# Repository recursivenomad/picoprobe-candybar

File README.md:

🍫 **A charming debug probe using the Raspberry Pi Pico**
=========================================================

### With a custom breakout, interface, and enclosure for Raspberry Pi's [Debug Probe][URL-Debug-Probe] firmware

[][URL-Repository]

***Features***
==============

Quick in-progress list:
- Logic level-shifting for interfacing with 5V/2.5V/1.8V boards (left switch)
- Power output selection (5V/none/3.3V) (right switch)
- 2 hardware interrupt breakpoints (rising & falling edge; left side pins)
- 9 pins wired for future implementation of a logic analyzer (3 analog, 3 logic level-shifted digital, 3 raw digital)
- Status LEDs (UART RX/TX, debug CONNECTED/RUNNING)
- Power rocker switch
- Debug access port for debugging with a second Picoprobe Candybar

***Cloning***
=============

```bash
git clone https://gitlab.com/recursivenomad/picoprobe-candybar.git
cd picoprobe-candybar/
git submodule update --init --single-branch
cd firmware/lib/debugprobe/
git config --local submodule.CMSIS_5.branch master
GIT_LFS_SKIP_SMUDGE=1 git submodule update --init --depth 1
git submodule foreach 'git fetch --depth 1'   # redundant, but gets the checked-out tag
cd ../../..
```

&nbsp;

***License / Access***
======================

This original work is freely available under your choice of the [*MIT-0*](./LICENSE.txt) license or [*CC0-1.0*][URL-CC0] public domain dedication.  
Although attribution is not required, sharing when you've made something with my work is really cool 💖

<details> <summary> <b><i>This work as a whole contains greater source code restrictions, fully listed here:</i></b> </summary>

  > Importing the [Debug Probe](https://github.com/raspberrypi/debugprobe/tree/debugprobe-v2.0.1/) submodule from Raspberry Pi introduces the following restrictions:  
  > *Linked to in [`./firmware/lib/`](./firmware/lib/)*
  >   - [*MIT License*][URL-MIT]
  >   - [*3-Clause BSD License*][URL-BSD-3-Clause]
  >   - [*Apache License, Version 2.0*][URL-Apache-2.0]
  >
  > Binaries are built using the [Pico SDK][URL-Pico-SDK] and [Arm GNU Toolchain][URL-ARM-Toolchain], and will add the following notices for distribution:
  >   - [*GCC Runtime Library Exception*][URL-GCC-Exception]
  >   - [*SunPro License*][URL-SunPro]
  >   - [*OAR License*][URL-OAR]
  >   - [*BSD 4.3 TAHOE License*][URL-BSD-4.3TAHOE]
  >   - [*Martin Birgmeier License*][URL-Martin-Birgmeier]

</details>

----------------------

*Repository: <https://gitlab.com/recursivenomad/picoprobe-candybar/>*  
*Contact: <recursivenomad@protonmail.com>*

----------------------

[URL-MIT-0]: <https://opensource.org/license/mit-0/>
[URL-CC0]: <https://creativecommons.org/publicdomain/zero/1.0/>

[URL-MIT]: <https://opensource.org/license/mit>
[URL-BSD-3-Clause]: <https://opensource.org/license/bsd-3-clause>
[URL-Apache-2.0]: <https://opensource.org/license/apache-2-0>

[URL-GCC-Exception]: <https://www.gnu.org/licenses/gcc-exception-3.0.en.html>
[URL-SunPro]: <https://spdx.org/licenses/SunPro.html>
[URL-OAR]: <https://spdx.org/licenses/OAR.html>
[URL-BSD-4.3TAHOE]: <https://spdx.org/licenses/BSD-4.3TAHOE.html>
[URL-Martin-Birgmeier]: <https://spdx.org/licenses/Martin-Birgmeier.html>

[URL-Repository]: <https://gitlab.com/recursivenomad/picoprobe-candybar/>

[URL-ARM-Toolchain]: <https://developer.arm.com/Tools%20and%20Software/GNU%20Toolchain>
[URL-Debug-Probe]: <https://github.com/raspberrypi/debugprobe/>
[URL-Pico-SDK]: <https://github.com/raspberrypi/pico-sdk>

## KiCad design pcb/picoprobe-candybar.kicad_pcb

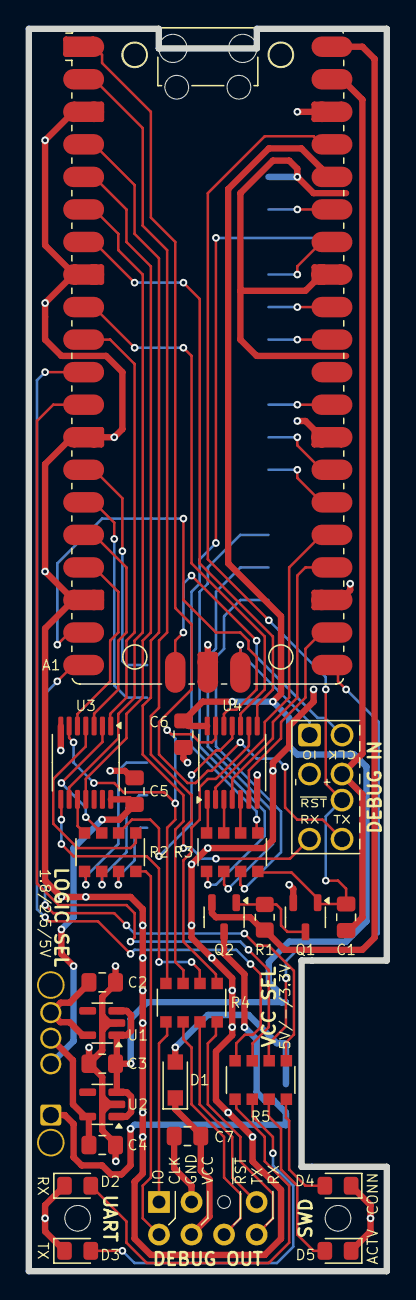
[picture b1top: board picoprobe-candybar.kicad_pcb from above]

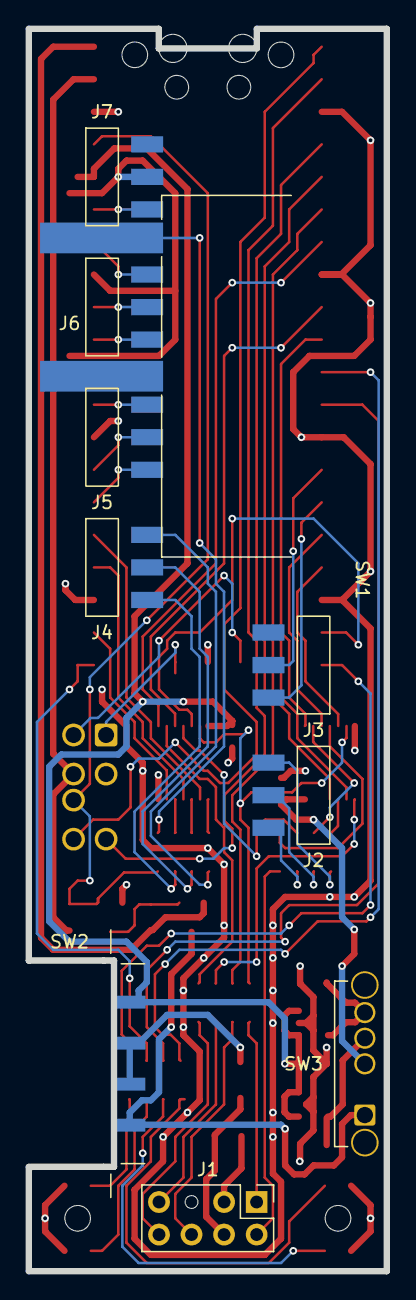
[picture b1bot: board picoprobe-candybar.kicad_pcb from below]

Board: 2 copper layers, 27.9 x 97.0 mm, 35 parts (10 on the bottom side), 68 nets.

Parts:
A1: RaspberryPi_Pico; RaspberryPi_Pico_Original_SMD_HandSolder
C1, C2, C3, C4, C5, C6, C7: 1u; C_0805_2012Metric_Pad1.18x1.45mm_HandSolder
D1: PMEG2010ER; Nexperia_CFP3_SOD-123W
D2: Orange; LED_0805_2012Metric_Pad1.15x1.40mm_HandSolder
D3: Yellow; LED_0805_2012Metric_Pad1.15x1.40mm_HandSolder
D4: Green; LED_0805_2012Metric_Pad1.15x1.40mm_HandSolder
D5: Red; LED_0805_2012Metric_Pad1.15x1.40mm_HandSolder
J0: SWD-UART_PicoprobeCandybar; SWD-UART_PicoprobeCandybar_PressFit_Compact
J1: PinHeader_2x04; PinHeader_2x04_P2.54mm_Vertical
J2, J3, J4, J5, J6, J7: PinHeader_1x03; PinHeader_1x03_P2.54mm_Horizontal_SMD
Q1: SSF2320Y; SOT-23-3
Q2: GSFC02501; SOT-23-3
R1: 100k; R_0805_2012Metric_Pad1.20x1.40mm_HandSolder
R2, R3, R4: 100R; R_Array_Convex_4x1206
R5: 470R; R_Array_Convex_4x1206
SW1: SW-R1-1A-E-1-0; SW_Rocker_SPST_QuickConnect_P10.8mm_SW-R1-1X-E-XX-0_Retrofi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
SW2: SLW-156646-5A-N-D; SW_Slide_SP3T_P3.2mm_CUI_SLW-156646-5A-N-D_Retrofit-SMD-Hor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
SW3: SLW-1277545-2A-RA-S-D; SW_Slide_SP3T_Common_Horizontal_P2mm_CUI_SLW-1277545-2A-RA-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
U1: TLV77318PDBVR; SOT-23-5
U2: TLV77325PDBVR; SOT-23-5
U3, U4: SN74LV6T17PWR; TSSOP-14_4.4x5mm_P0.65mm

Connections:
1V8: C2.1, SW3.4, U1.5 (OUT)
2V5: C4.1, SW3.3, U2.5 (OUT)
3V3: A1.36 (3V3), C3.1, C6.1, SW2.1, U1.1 (IN), U1.3 (EN), U2.1 (IN), U2.3 (EN), U4.14 (VCC)
5V: Q2.3 (D), SW2.4, SW3.1
/3V3_EN: A1.37 (3V3_EN), C1.2, J0.6 (~RESET), Q1.1 (G), R3.4 (R4.1)
/ADC0: A1.31 (GPIO26_ADC0), J6.1
/ADC1: A1.32 (GPIO27_ADC1), J6.2
/ADC2: A1.34 (GPIO28_ADC2), J6.3
/ADC_VREF: A1.35 (ADC_VREF), J7.1
/CB_CLK: J1.2, R2.4 (R4.1)
/CB_CTS: J2.3, R2.3 (R3.1)
/CB_DTR: J2.1, R2.1 (R1.1)
/CB_IO: J1.1, R4.1 (R1.1)
/CB_RS1: J4.1, R3.3 (R3.1)
/CB_RS2: J4.2, R3.2 (R2.1)
/CB_RS3: J4.3, R3.1 (R1.1)
/CB_RS4: A1.26 (GPIO20), J5.1
/CB_RS5: A1.27 (GPIO21), J5.2
/CB_RS6: A1.29 (GPIO22), J5.3
/CB_RTS: J2.2, R2.2 (R2.1)
/CB_RX: J1.8, R4.4 (R4.1)
/CB_TX: J1.7, R4.3 (R3.1)
/CB_~RST: J1.6, R4.2 (R2.1)
/CLK: A1.16 (GPIO12), U3.3 (2A)
/CTS: A1.9 (UART1_CTS), U4.10 (5Y)
/DTR: A1.5 (GPIO3), U3.11 (5A)
/INT_FALL: A1.15 (GPIO11), J3.3
/INT_RISE: A1.14 (GPIO10), J3.2
/IO_IN: A1.19 (GPIO14), U4.12 (6Y)
/IO_OUT: A1.17 (GPIO13), U3.5 (3A)
/IO_SHIFTED: R4.8 (R1.2), U3.6 (3Y), U4.13 (6A)
/LED_CON: A1.20 (GPIO15), R5.5 (R4.2)
/LED_RUN: A1.21 (GPIO16), R5.6 (R3.2)
/LED_RX: A1.12 (GPIO9), R5.7 (R2.2)
/LED_TX: A1.11 (GPIO8), R5.8 (R1.2)
/RS1: A1.22 (GPIO17), U4.6 (3Y)
/RS2: A1.24 (GPIO18), U4.4 (2Y)
/RS3: A1.25 (GPIO19), U4.2 (1Y)
/RTS: A1.10 (UART1_RTS), U3.1 (1A)
/RX: A1.7 (UART1_RX), U4.8 (4Y)
/TX: A1.6 (UART1_TX), U3.9 (4A)
/~RST: A1.4 (GPIO2), R4.7 (R2.2)
AGND: A1.33 (AGND), J7.2
GND: A1.3 (GND), A1.8 (GND), A1.13 (GND), A1.18 (GND), A1.23 (GND), A1.28 (GND), A1.38 (GND), A1.D2 (GND), C2.2, C3.2, C4.2, C5.2, C6.2, C7.2, D2.1 (K), D3.1 (K), D4.1 (K), D5.1 (K), J0.3 (GND), J1.3, J7.3, Q1.2 (S), SW1.1 (A), U1.2 (GND), U2.2 (GND), U3.7 (GND), U4.7 (GND)
unnamed: A1.1 (UART0_TX), J0.8 (UART_RX)
unnamed: A1.2 (UART0_RX), J0.7 (UART_TX)
unnamed: A1.D1 (SWCLK), J0.2 (SWCLK)
unnamed: A1.D3 (SWDIO), J0.1 (SWDIO)
unnamed: D1.2 (A), SW2.2, SW2.3
unnamed: D2.2 (A), R5.1 (R1.1)
unnamed: D3.2 (A), R5.2 (R2.1)
unnamed: D4.2 (A), R5.4 (R4.1)
unnamed: D5.2 (A), R5.3 (R3.1)
unnamed: Q1.3 (D), Q2.1 (G), R1.1
unnamed: R2.8 (R1.2), U3.10 (5Y)
unnamed: R2.7 (R2.2), U3.2 (1Y)
unnamed: R2.6 (R3.2), U4.11 (5A)
unnamed: R2.5 (R4.2), U3.4 (2Y)
unnamed: R3.8 (R1.2), U4.1 (1A)
unnamed: R3.7 (R2.2), U4.3 (2A)
unnamed: R3.6 (R3.2), U4.5 (3A)
unnamed: R3.5 (R4.2), SW1.2 (B)
unnamed: R4.6 (R3.2), U3.8 (4Y)
unnamed: R4.5 (R4.2), U4.9 (4A)
VBUS: A1.40 (VBUS), Q2.2 (S), R1.2
VLOGIC: C5.1, SW3.2, U3.14 (VCC)
VOUT: C7.1, D1.1 (K), J1.4
VSYS: A1.39 (VSYS), C1.1, J0.4 (VCC)

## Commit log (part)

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2024-06-22 Initialize KiCad project
    KiCad 8.0.3
2024-06-23 Add ki-lime-pi-to-go submodule
    Ki-Lime Pi Pico 2.0.0
2024-06-24 Ignore autosaves
2024-06-25 Register compact-title-block
2024-06-30 Add CC0 as elective dual license
2024-06-30 Embrace Ki-Lime Pi Pico library name
2024-06-30 Update kicad-title-block for standardized license
2024-06-30 Remove SPDX text for GitHub's license recognition
2024-06-30 Bump submodules for unified license text
2024-07-03 Add debugprobe submodule
    Debug Probe v2.0.1
2024-07-03 Change PROJECT_NAME
2024-07-03 Override with definitions specific to Candybar
    - Adding target reset support
    - Using the onboard LED for USB indication
    - Applying a custom USB device name
2024-07-03 Remove existing UART feature descriptions
2024-07-03 Create license info binary declaration macros
2024-07-04 Update tools and library path in attributions
2024-07-26 Simplify .gitmodules
2024-07-26 Rename title block directory
2024-07-26 Don't track a specific branch for Ki-Lime Pi Pico
2024-07-26 Add picoprobe-candybar-interface submodule
    Version 0.1.0
2024-07-26 Spacing
2024-07-29 Update picoprobe-candybar-interface submodule
    0.1.1
2024-07-29 Add IDC cable connector
2024-07-29 Ignore .bak files
2024-07-29 Add 74AUP1T17 per Debug Probe schematic
    <https://assets.nexperia.com/documents/data-sheet/74AUP1T17.pdf>
    <https://datasheets.raspberrypi.com/debug/raspberry-pi-debug-probe-schematics.pdf>
2024-07-29 Rename project-specific library directory
2024-07-29 Initial IDC connector layout
2024-07-29 Duplicate to create UART pins
2024-07-29 Connect Pico & (debugger's own) debug interface
2024-07-29 ERC: Don't short VSYS/VBUS
2024-07-29 Centre diode symbol
    Technically "off-grid" to KLC, but follows convention of other diodes
2024-07-29 ERC: Replace colliding label with non-label text
2024-07-30 Emphasize Raspberry Pi attribution
2024-07-30 Update title blocks to reflect unreleased state
2024-07-31 Adjust GND/power positioning
2024-07-31 Reposition all elements
2024-07-31 Change nRST pin to GPIO3
    Was previously rolling with the Debug Probe default of GPIO1, but that
    definition appears to be due to Debug Probe's limited pinout [1].
    This schematic will read easier if GPIO1 isn't shared.
    (Plus UART0 probably wouldn't have worked if this firmware needed to be
    debugged when it was shared with nRST)
    [1]: <https://github.com/raspberrypi/debugprobe/pull/123#issuecomment-1964397931>
2024-08-01 Add SP3T switch for selecting VCC source
2024-08-01 Layout slide switch symbol
2024-08-01 Generalize symbol name
2024-08-01 Initialize SP3T footprint
2024-08-01 Add SP3T pins
2024-08-01 Draw SP3T Fab and Courtyard
2024-08-01 Add silkscreen outline
2024-08-01 Add SP3T footprint filter
2024-08-01 Add datasheet to SP3T footprint description
2024-08-01 Specify part number for SP3T switch
2024-08-01 Nudge power symbol labels to align to grid
2024-08-02 Swap inputs 1 & 4 on SW1 for better MOSFET pos
2024-08-02 Connect VBUS MOSFET
    VBUS will still be powered over USB even when 3V3_EN is pulled low.
    This FET ensures that VBUS only delivers power to the target when 3V3 is
    supplied.
2024-08-02 Add datasheet to uniquely specified symbols
2024-08-02 Add generic power switch
2024-08-02 Hide SW2 pin numbers
2024-08-02 Initialize rocker switch custom footprint
    This one's gonna be interesting
2024-08-02 Add placeholder model for rocker switch
    It's a hilariously scaled resistor
2024-08-03 Reindex symbols
2024-08-03 Change LED colours
    Green: Connected
    Orange: Controlling/Transmitting
    Yellow: Receiving
2024-08-03 Rename IDC header
2024-08-09 Change D1 from MBR120VLSF to PMEG6010ELR
    Following suit of the more affordable VBUS protection diode found in the
    Raspberry Pi Pico 2
    <https://datasheets.raspberrypi.com/pico/pico-2-datasheet.pdf#schematic>
2024-08-09 Clarify substitutable component constraints
2024-08-09 Schematic repositioning
2024-08-10 Fix RC filter source to use VSYS
    Also sets VSYS as a power symbol
2024-08-10 Rename +3V3 to 3V3
2024-08-10 Revert MOSFET pull-down resistor
    This reverts commit 6fe8bc9f0c940ba738d5339ab096eecd7118b4fd.
2024-08-10 Fix VBUS MOSFET polarity
    Incorrectly used N-Channel when the design calls for P-Channel
2024-08-11 Add N-channel MOSFET to control VBUS MOSFET
2024-08-11 Hide MOSFET pin numbers
2024-08-11 Update schematic with switch symbol's outline
2024-08-12 Relocate CTS/RTS to GPIO6/7
    This displaces the non-level-shifted CB_RX (which is actually a good
    thing, as now GPIO9 can be set to UART1_RX if desired)
    Also displaces the UART_RX_LED
    Leaves GPIO11 unassigned for future possible SWDOEN use
2024-08-12 Move nRESET to GPIO2
    Also swaps UART_DTR to GPIO3, logically grouping all UART pins together.
2024-08-12 Connect GPIO11 to 1x01 socket for future use
    Possible future SWDIOEN support
2024-08-12 Reposition and label schematic
2024-08-12 Specify hardware flow control directionality
2024-08-14 Remove GPIO 11 socket
    Clarified possible future use of SWDIOEN is meant for internal signals
    <https://github.com/raspberrypi/debugprobe/issues/147>
2024-08-14 Use generic diode symbol (& delete custom diode)
2024-08-14 Increase component label spacing for legibility
2024-08-14 Remove previous level-shifter 74AUP1T17
2024-08-14 Disconnect GPIO9
    UART_RX shouldn't need a redundant non-shifted input
2024-08-14 Isolate interface GPIO in prep for level-shifters
2024-08-14 Swap UART LED schematic hierarchy
2024-08-14 Add MicroPak to NC7WZ17 footprint filter
2024-08-14 Make NC7WZ17 symbol more compact
2024-08-14 Add logic level-shifting array
2024-08-14 Alighn endpoint I/O to schematic right
2024-08-15 Add SW_Slide_SP3T_Common_MBBR symbol
2024-08-15 Add SLW-1277545-2A-RA-S-D switch symbol
    Uses placeholder 3D model
2024-08-15 Make SW_Slide_SP3T_Common_MBBR thinner
2024-08-16 Fix input logic to use 3V3 source
2024-08-16 Change NC7WZ17 to SN74LV6T17
    Previous buffer did not have a wide enough level translation range.
    Also, turns out this'll be cheaper at low-volume orders. Nice.
2024-08-16 Reposition and add 1.8V & 2.5V regulators
2024-08-16 Change on/off cap to 1u
    Already have 1u on the board now for regulators, and this gets the
    debounce filtering above "the" 20ms threshold.
    <https://www.eejournal.com/article/ultimate-guide-to-switch-debounce-part-4/>
2024-08-16 Hide 3V3_EN junction due to internal pull-up
2024-08-17 Repositioning & spacing
2024-08-17 Expose GPIO17-19 as level-shifted input
    Hoping to implement these as level-shifted sigrok digital inputs someday
    See here for Picoprobe sigrok inspiration:
    <https://github.com/pico-coder/sigrok-pico>
    <https://github.com/perexg/picoprobe-sump/tree/logic-analyzer>
    <https://github.com/rgrr/yapicoprobe/blob/master/doc/sigrok.adoc>
2024-08-17 Directly expose ADC0-2 for future use
    Also with hopes of future sigrok implementation
2024-08-17 Repositioning
2024-08-17 Re-place internal pull-up for export rendering
2024-08-18 Prepare for 0.1.0 pre-release & add BUILDING.md
2024-08-18 Update schematic annotations
2024-08-18 Remove board keepout area from rocker switch
    Was originally planning to have it nestle into a void on the board, but
    with how I'm thinking of stacking it below the Pico it'll need to rest
    on the board like a typical SMD component. It'll be interesting.
2024-08-18 Re-add rocker keep out specifically to overhang
2024-08-18 Relocate rocker switch origin to exterior surface
    Might make board layout alongside MCAD easier.
2024-08-18 Reduce pad size of horizontal slide switch
    Previous size was creating DRC errors due to mounting hole dimensions
2024-08-18 Mirror rocker switch footprint
2024-08-19 Change Q1 from SSM3K35AMFV to T2N7002AK
    Previous package was too small for accessible hand-soldering.
    Now all 3-5 pin ICs are SOT-23. Nice.
2024-08-19 Change GND socket to AGND
2024-08-19 First scratch compact board layout (ratsnest)
2024-08-19 Mirror uncvonventional SMD slide switch footprint
2024-08-20 Set retrofit SMD pins to type "Edge Connector"
2024-08-20 Resize rocker SMD pad to match pin length
2024-08-20 Swap rocker footprint pins 1 & 2
    Better to have GND under AGND than the 3V3_EN signal.
    Also now accurately reflects which terminal is breakable on schematic.
2024-08-21 Start adding silkscreen labels
2024-08-27 Formatting
2024-08-28 Ignore .clangd
2024-08-28 Define empty interrupt for GPIO10/11
2024-09-01 Reorder #includes hierarchically
2024-09-01 Fix *.clangd typo
2024-10-30 Comment regarding interrupt safety
2024-10-31 Add -Wall toggle in CMakeLists.txt
2024-10-31 Specify void parameters in function declarations
2024-10-31 Change -Wall toggle to an always-on conditional
2024-10-31 Re-add option for toggling non-imported warnings
2024-10-31 Rename candybar_binary_config.c before merge
2024-11-01 Revise LED colours
    Green: Connected
    Red: Controlling/Halted
    Orange: Transmitting
    Yellow: Receiving
2024-11-01 Expand mounting hole copper clearance
    Also adjusts some silkscreen text
2024-11-01 First pass trace layout (power & proximity)
2024-11-02 Major rework (prioritize debug signal integrity)
2024-11-05 Rewire debug lines 1
2024-11-07 Incremental Rewire debug lines 2
2025-05-09 Don't level-shift nRESET output signal
    Needs to behave as an open drain
2025-05-10 Rename GPIO labels
2025-05-10 Move 100R from `CB_RST` to On/Off switch
    `CB_RST` signal, if used, is not high-frequency, and thus does not need
    a termination resistor.
    On/Off switch series resistor simply needs to be below ~8k due to
    voltage division (see commit `b02ed6a` for details)
    RC charge ("Off") speed does not matter, and switch series resistor
    value does not change the >20ms RC discharge ("On") speed
2025-05-10 Replace 1x02 interrupt socket with 1x03
    Limits BOM entries
2025-05-10 Add `PWR_FLAG` to `ADC_VREF`
    Happy ERC :)
2025-05-10 Update components in draft layout
    Layout still heavily in-progress
2025-05-12 Major in-progress layout redesign
2025-05-13 Continue refining layout; add SMD PinHeader
2025-05-14 Adjust placeholder switch model scales/positioning
    This way the switch protrusion is accurately visualized
2025-05-14 Continue refining layout; accommodate courtyards
2025-05-14 Reposition LOGIC SEL switch to be flush w/ housing
2025-05-14 Use compact interface for DEBUG IN
2025-05-15 Create some wider openings for ground plane
2025-05-15 Change Q2 out for an available alternative
    Original DMP31D1U was on backorder on Digi-Key.
2025-05-15 Change Q1 out for a cheaper alternative
2025-05-15 Specify horizontal PinHeader_1x03 product number
    The fit is tight, and certain substitutes may not work as well,
    so defining this as a default in the BOM.
2025-05-15 Update datasheet URLs
2025-05-15 Update part names to fully resolved names
    Tested via Digi-Key list upload:
    <https://www.digikey.com/en/mylists/>
2025-05-15 Add second TestHooks_x06 BOM entry
    For a total of 12 test hooks.
2025-05-15 Update license year
2025-05-17 Add `pre-commit.sh`
2025-05-17 Instantiate parametric STEP/VRML export structure
2025-05-19 Restructure parametric element naming
2025-05-19 Create Cable_Plug_Cap model
2025-05-19 Create Cable_Wires
2025-05-19 Initialize keyed PinHeader model structure
2025-05-19 Fix "MissingPinNumber" ID
2025-05-19 Create PinHeader_2x04
2025-05-19 Add hole to header Pin 5 location
2025-05-19 Give VRMLs standard name
    KiCad StepUp will export based on VRML export name
2025-07-24 Re-commit .FCStd for graceful recomputation
2025-07-25 Update Plug Cap to more closely reflect real part
2025-07-25 Add pin holes & set VRML colours for export
2025-07-26 Add merge commit escape to pre-commit hook

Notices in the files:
pcb/picoprobe-candybar.kicad_pcb:
MIT-0 OR CC0-1.0
